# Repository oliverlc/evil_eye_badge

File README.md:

A simple project for experimenting with creating a PCB with a more creative than functional purpose. Taking inspiration from people in the USA who create badges for conferences for fun, art, and to show off.

These badges are a simple skull graphic, with a ATTINY10 microcontroller fading in and out two LEDS in the skulls eye sockets. The LEDS fade in over a second, remain on for 5 seconds, fade out over another second, then remain off for 30 seconds (ish) before repeating.

The process involved:
    • Finding a vector image I was happy with (I’m no graphic artist)
    • Splitting the vector image into layers using Inkscape
    • Importing the layers I’ve created into KiCad using SVG2MOD
    • Adding a functional circuit (a micro controller driving two PWM leds)
    • Getting the boards made
    • Populating the boards
    • ?????
    • Profit! (If only!)

I was wearing these badges at the bi-annual UK hacker camp ElectroMagnetic Field (EMF). They didn’t quite get the interest I expected. Perhaps they were over-shadow by another of my projects: the LED light staff!

The KiCad and Gerber files using the skull graphic from vectormagic.com are notable only by their absence. Apologies for that. I wanted to make sure I was on the right side of their licence and wasn't sure if this would count as distributing via another website. I assume their licence is referring to distributing the vector original but don't want to risk it.

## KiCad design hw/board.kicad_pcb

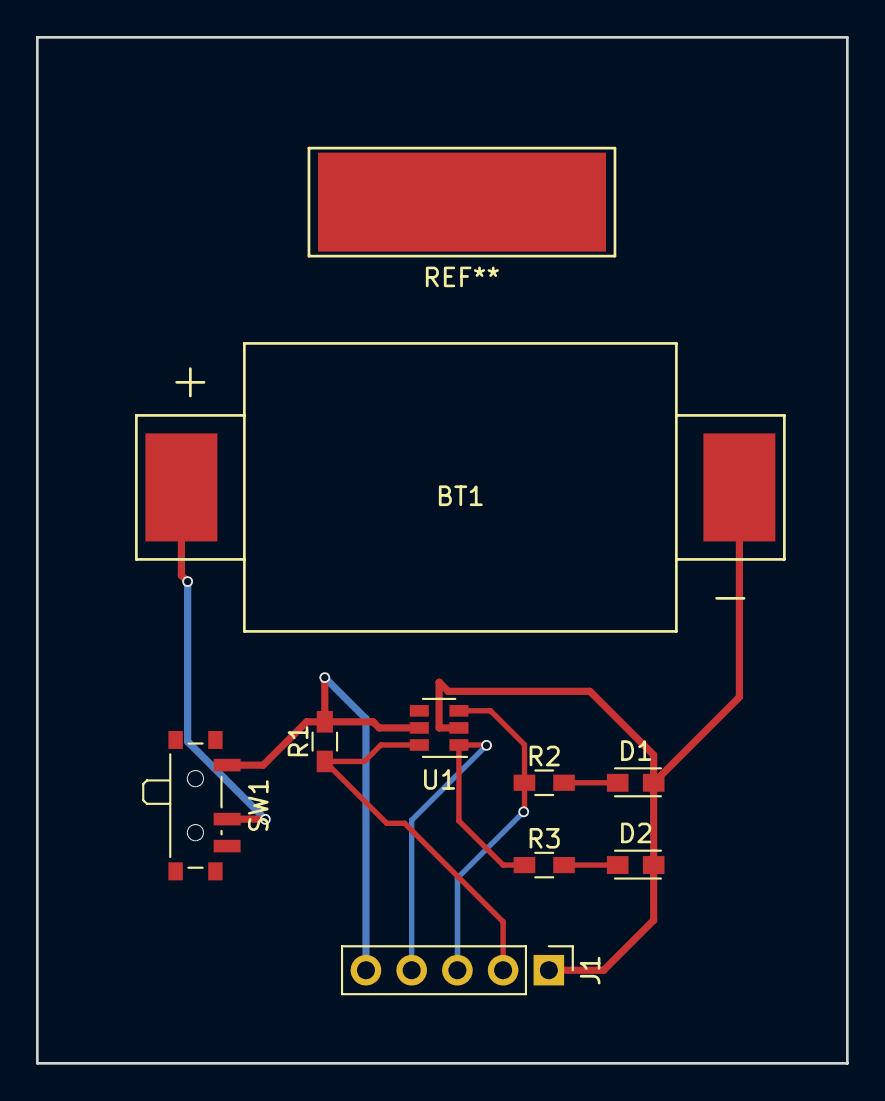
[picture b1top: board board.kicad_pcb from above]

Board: 2 copper layers, 45.0 x 57.0 mm, 9 parts (0 on the bottom side), 8 nets.

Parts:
BT1: Battery_Cell; Battery_holder_CR2032
D1, D2: LED; LED_miniPLCC_2315_Handsoldering
J1: Conn_01x05; Pin_Header_Straight_1x05_Pitch2.54mm
R1: DNF; R_0603_HandSoldering
R2, R3: 120R; R_0603_HandSoldering
SW1: SW_DIP_x01; SW_SPDT_PCM12
U1: ATTINY10-TS; SOT-23-6

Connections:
/3Vcc: BT1.1, SW1.2
/RESET: J1.2, R1.1, U1.6
/TPICLK: J1.3, R2.1, U1.3
/TPIDATA: J1.4, R3.1, U1.1
/VCC: J1.5, R1.2, SW1.1, U1.5
GND: BT1.2, D1.1, D2.1, J1.1, U1.2
unnamed: D1.2, R2.2
unnamed: D2.2, R3.2

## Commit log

2018-09-09 Added images of final badge v1
2018-09-09 Gah, typo
